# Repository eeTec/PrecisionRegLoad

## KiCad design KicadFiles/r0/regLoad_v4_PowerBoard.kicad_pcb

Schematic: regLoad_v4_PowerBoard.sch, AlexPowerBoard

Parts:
C1, C2, C6, C9: 1uF; SparkFun-Capacitors-0603-CAP
C3, C5, C17, C22, C23, C24: 4.7uF; SparkFun-Capacitors-0603-CAP
C4, C10, C15, C21: 100n; SparkFun-Capacitors-0603-CAP
C7: 0.1uF; SparkFun-Capacitors-0603-CAP
C8, C12, C14, C16: .1uF; SparkFun-Capacitors-0603-CAP
C13, C18, C20: 2.2uF; SparkFun-Capacitors-0603-CAP
C19: 10n; SparkFun-Capacitors-0603-CAP
D1: DIODE-ZENER3.3V; SparkFun-DiscreteSemi-SOD-123
J1: M01PTH_2MM; SparkFun-Connectors-1X01_2MM
J2, J3: M01PTH_2MM; 5mm_Connector
J4, J5: UART_ISO; PH-Connector-TopEntry
L1, L2: FER; SparkFun-Passives-0603-RES
LED1: 5v; adafruit-CHIP-LED0603
LED2: 3.3v; adafruit-CHIP-LED0603
P1, P3, P6, P9, P11, P12, P14, P15, P16, P17, P18, P19: test; SparkFun-Connectors-1X01_POGOPIN_HOLE_0.58
P2: CONN_01X01; Shield_2x3cm
Q3, Q4, Q5, Q6: IIRLZ44; TO-220
R1, R3, R4, R6: 2.2k; SparkFun-Passives-0603-RES
R2, R5, R7, R8: 1k; SparkFun-Passives-0603-RES
R11, R13, R15, R17: 100; SparkFun-Passives-0603-RES
R12, R14, R16, R19, R20: 0.01; adafruit-R2512
SJ1, SJ2, SJ3: SOLDERJUMPER_2WAY-OLDPASTE1&2; Solderjumper_PRE
U1: MCP4725SOT-23; adafruit-SOT23-6
U2: LM75_Bottom; SparkFun-AnalogIC-SO08
U3, U5, U6: LM358; SparkFun-AnalogIC-SO08
U4: MCP3426-8SOIC; SOIC-8-1EP_3.9x4.9mm_Pitch1.27mm
U7: AD8215; SparkFun-AnalogIC-SO08
U8: TPS793; SparkFun-AnalogIC-SOT23-5

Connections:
+3V3: C1.1, C2.1, C3.1, C10.1, C16.1, C20.1, C21.1, C23.1, C24.1, J5.1, LED2.A, SJ1.1, SJ1.2, SJ2.1, SJ2.2, SJ3.1, SJ3.2, U1.3 (VDD), U1.6 (AO), U2.6 (A1), U2.7 (A0), U2.8 (VCC), U4.3 (VDD), U7.6 (VCC), U8.5 (OUT)
+5V: C5.1, C7.1, C8.1, C12.1, C13.1, C14.1, C17.1, C22.1, L2.1, LED1.A, U3.8 (V+), U5.8 (V+), U6.8 (V+), U8.1 (IN), U8.3 (EN)
CURRENT: R6.2, U7.5 (OUT)
GND: C1.2, C2.2, C3.2, C4.2, C5.2, C6.2, C7.2, C8.2, C9.2, C10.2, C12.2, C13.2, C14.2, C15.2, C16.2, C17.2, C18.2, C19.2, C20.2, C21.2, C22.2, C23.2, C24.2, D1.A, J3.1, J4.4, J5.4, P2.1, R2.2, R4.1, R7.2, R8.2, R12.2, R14.2, R16.2, R19.2, SJ1.3, SJ2.3, SJ3.3, U1.2 (VSS), U2.4 (GND), U2.5 (A2), U3.4 (V-), U4.2 (CH1-), U4.6 (GND), U4.8 (CH2-), U4.9 (GND), U5.3 (+), U5.4 (V-), U6.4 (V-), U7.2 (GND), U8.2 (GND)
unnamed: C4.1, R3.2, U5.5 (+)
unnamed: C6.1, D1.C, P16.1, R2.1, R5.1, U4.1 (CH1+)
unnamed: C9.1, P18.1, R6.1, U4.7 (CH2+)
unnamed: C15.1, L1.1, L2.2
unnamed: C18.1, J4.1, L1.2
unnamed: C19.1, U8.4 (NR)
unnamed: J2.1, R20.1, U7.8 (+IN)
unnamed: LED1.C, R7.1
unnamed: LED2.C, R8.1
unnamed: P1.1, R3.1, U1.1 (VOUT)
unnamed: P3.1, R1.2, R4.2, U3.3 (+), U3.5 (+), U5.7, U6.3 (+), U6.5 (+)
unnamed: P6.1, Q3.3 (S), R12.1, U3.2 (-)
unnamed: P9.1, R11.2, U3.1
unnamed: P11.1, Q4.3 (S), R14.1, U3.6 (-)
unnamed: P12.1, R13.2, U3.7
unnamed: P14.1, Q5.3 (S), R16.1, U6.2 (-)
unnamed: P15.1, Q5.1 (G), R15.1
unnamed: P17.1, Q6.3 (S), R19.1, U6.6 (-)
unnamed: P19.1, R17.2, U6.7
unnamed: Q3.1 (G), R11.1
unnamed: Q3.2 (D), Q4.2 (D), Q5.2 (D), Q6.2 (D), R20.2, U7.1 (-IN)
unnamed: Q4.1 (G), R13.1
unnamed: Q6.1 (G), R17.1
unnamed: R1.1, U5.6 (-)
unnamed: R15.2, U6.1
unnamed: U5.1, U5.2 (-)
unnamed: U7.4 (NC), U7.7 (NC)
SCL: J4.2, J5.2, U1.5 (SCL), U2.2 (SCL), U4.5 (SCL)
SDA: J4.3, J5.3, U1.4 (SDA), U2.1 (SDA), U4.4 (SDA)
VSENSE: J1.1, R5.2

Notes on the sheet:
POWERSINK/LOAD_UNIT
Reference ADC

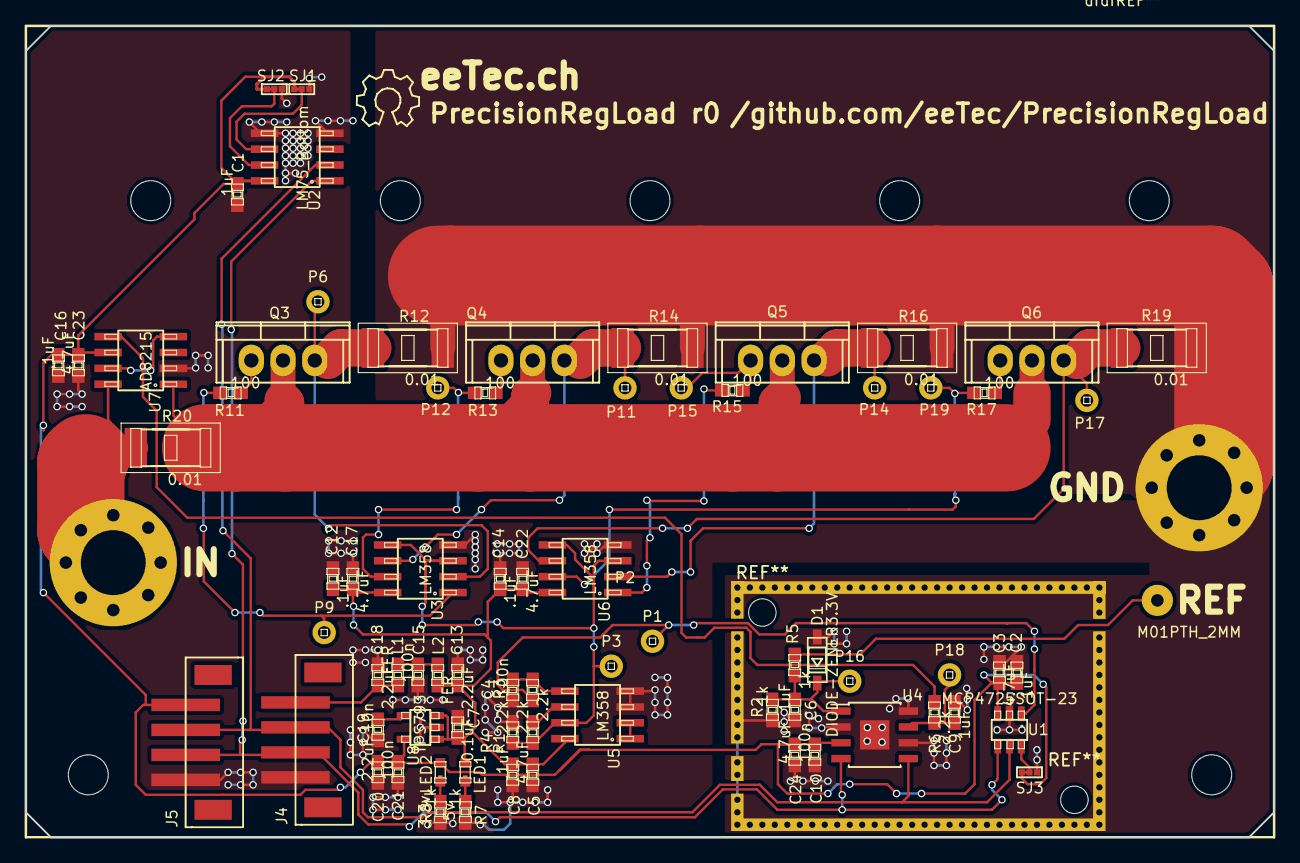
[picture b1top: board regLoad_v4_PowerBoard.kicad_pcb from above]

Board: 2 copper layers, 100.0 x 65.0 mm, 83 parts (0 on the bottom side), 34 nets.

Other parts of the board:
REFdfdf**: MountingHole_3.2mm_M3
RdfdfEF**: MountingHole_3.2mm_M3
RdfdfdEF**: MountingHole_3.2mm_M3
ddfdREF**: MountingHole_3.2mm_M3
dfdfREF**: MountingHole_3.2mm_M3

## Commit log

2016-09-02 First commit, some tests done, looks good but use with care!!!
